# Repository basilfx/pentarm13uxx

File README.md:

pentarm13uxx
============

A small template project (blinking led) for the new lpc1347 (successor of the popular lpc1343).

Including Makefile, linker-script and cmsis and microcontroler header files.

Also includes eagle files for a small breaboardable eval-board.

- - -

####lpc1347 features

* 12k sram (was 8k)
* 64k flash (was 32k)
* 4k EEPROM (new)
* 72Mhz
* USART,I2C,2xSPI
* 12Bit ADC (new)
* USB_MSC, USB_HID, USB_CDC and USB_DFU in rom (new)
* usb-bootloader in rom

- - -

price of the eval board: ~$15

- - -

####BOM:

* C1,C2 : 22pF 0402
* C3,C4 : 100nF 0402
* C6,C8 : 10nF 0402
* C5,C7 : 1µF 0805
* R2,R3,R6,R7 : 150R 0402
* R4,R5 : 33R 0402
* R1,R8,R9 : 15k 0402
* R10 : 1k5 0402
* T1 : Si3102DS SOT23 (or other pfet)
* Q1 : 12Mhz MT (farnell: 1842056)
* IC1 : lpc1347 QFP48 (farnell: 2103477)
* IC2 : LT1763CS8-3.3 SOIC8 (farnell: 1273617)
* X1 : Mini USB Connector SMD (farnell: 1125348)
* X2,X3 : Pin-Header 10 Pin
* X4 : Pin Header 2 Pin
* X5 : Pin Header 4 Pin
* LED1 : RGB LED PLCC4 common annode
* SW1,SW2,RST : MCTAEF-25N (farnell:1605484)

- - -

data sheet  : http://www.nxp.com/documents/data_sheet/LPC1315_16_17_45_46_47.pdf

user manual : http://www.nxp.com/documents/user_manual/UM10524.pdf

toolchain   : https://launchpad.net/gcc-arm-embedded

- - -   

Board top render

 Completed boards, photo by [Dirk Soeteman](http://www.dirksoeteman.nl/)

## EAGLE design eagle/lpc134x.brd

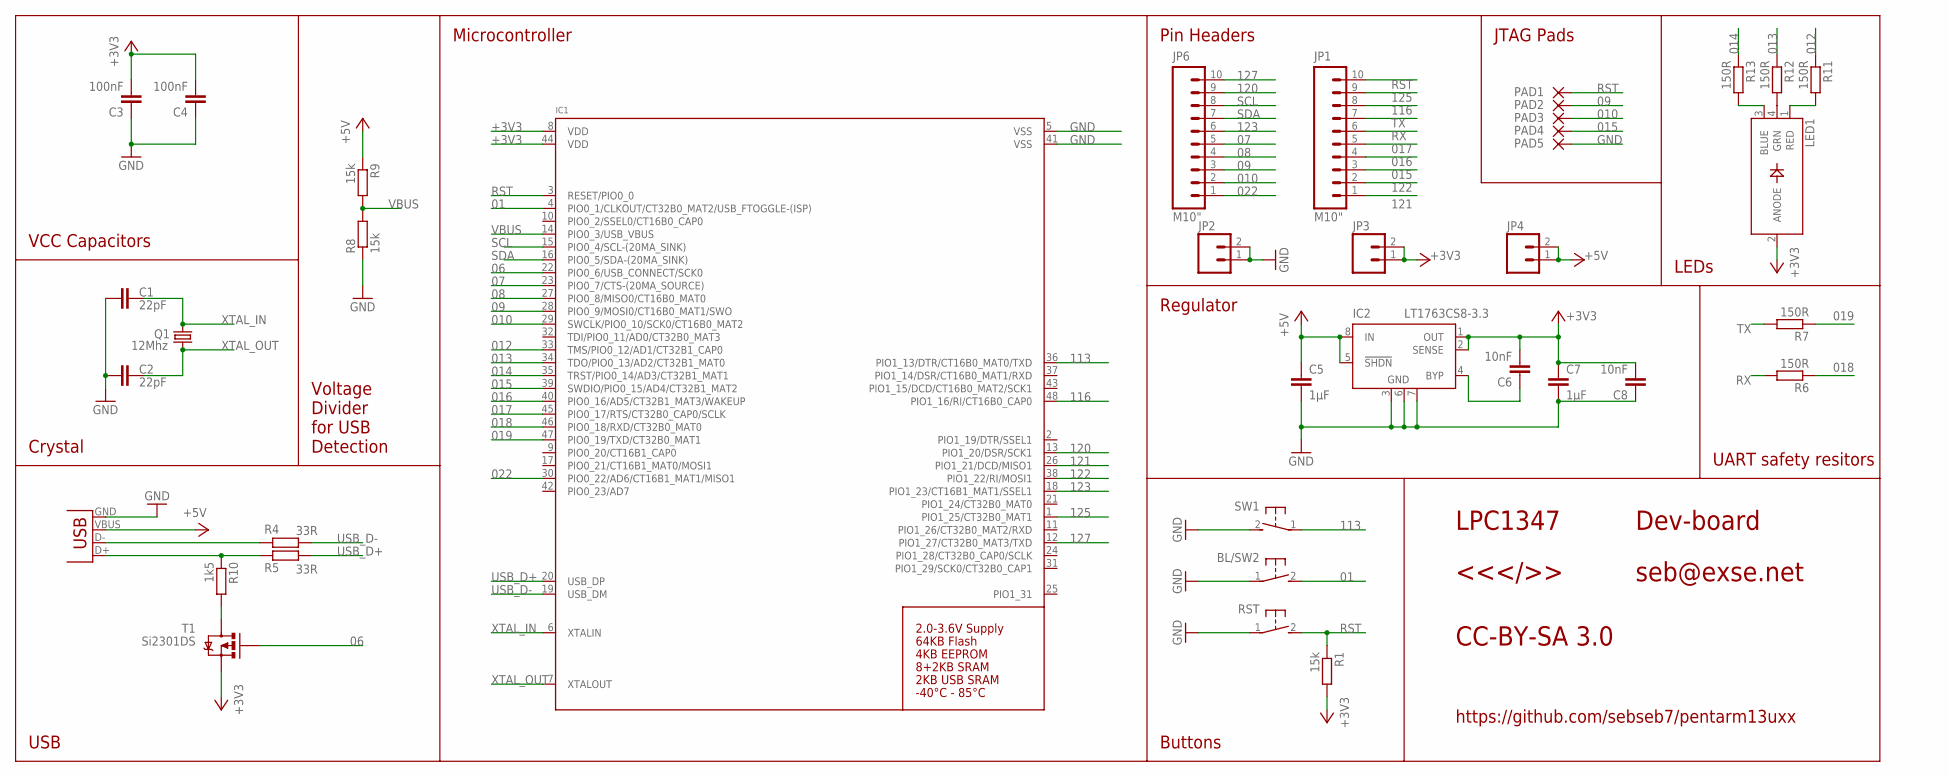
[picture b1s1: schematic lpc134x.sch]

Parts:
BL/SW2: SWITCH_MCTAEF
C1, C2: 22pF; C0402
C3, C4: 100nF; C0402
C5, C7: 1µF; 0805
C6, C8: 10nF; C0402
IC1: LPC1347_QFP48; LQFP48
IC2: LT1763CS8-3.3; SOIC8
JP1, JP6: M10"; 1X10
JP2, JP3, JP4: M02PTH; 1X02
LED1: LED_RGB_PLCC4; RGBLED_PLCC4
PAD1, PAD2, PAD3, PAD4, PAD5: WIREPADSMD1,27-254; SMD1,27-2,54
Q1: 12Mhz; MT
R1, R8, R9: 15k; R0402
R4, R5: 33R; R0402
R6, R7, R11, R12, R13: 150R; R0402
R10: 1k5; R0402
RST: SWITCH_MCTAEF
SW1: SWITCH_MCTAEF
T1: Si2301DS; SOT23
X2: USB-SMD-NS; USB-MINIB-NOSTOP

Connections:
01: BL/SW2.2, IC1.4 (PIO0_1/CLKOUT/CT32B0_MAT2/USB_FTOGGLE-(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)
06: IC1.22 (PIO0_6/USB_CONNECT/SCK0), T1.1 (G)
07: IC1.23 (PIO0_7/CTS-(20MA_SOURCE)), JP6.5
08: IC1.27 (PIO0_8/MISO0/CT16B0_MAT0), JP6.4
09: IC1.28 (PIO0_9/MOSI0/CT16B0_MAT1/SWO), JP6.3, PAD2.1
010: IC1.29 (SWCLK/PIO0_10/SCK0/CT16B0_MAT2), JP6.2, PAD3.1
012: IC1.33 (TMS/PIO0_12/AD1/CT32B1_CAP0), R11.1
013: IC1.34 (TDO/PIO0_13/AD2/CT32B1_MAT0), R12.1
014: IC1.35 (TRST/PIO0_14/AD3/CT32B1_MAT1), R13.1
015: IC1.39 (SWDIO/PIO0_15/AD4/CT32B1_MAT2), JP1.3, PAD4.1
016: IC1.40 (PIO0_16/AD5/CT32B1_MAT3/WAKEUP), JP1.4
017: IC1.45 (PIO0_17/RTS/CT32B0_CAP0/SCLK), JP1.5
018: IC1.46 (PIO0_18/RXD/CT32B0_MAT0), R6.1
019: IC1.47 (PIO0_19/TXD/CT32B0_MAT1), R7.1
022: IC1.30 (PIO0_22/AD6/CT16B1_MAT1/MISO1), JP6.1
113: IC1.36 (PIO1_13/DTR/CT16B0_MAT0/TXD), SW1.1
116: IC1.48 (PIO1_16/RI/CT16B0_CAP0), JP1.8
120: IC1.13 (PIO1_20/DSR/SCK1), JP6.9
121: IC1.26 (PIO1_21/DCD/MISO1), JP1.1
122: IC1.38 (PIO1_22/RI/MOSI1), JP1.2
123: IC1.18 (PIO1_23/CT16B1_MAT1/SSEL1), JP6.6
125: IC1.1 (PIO1_25/CT32B0_MAT1), JP1.9
127: IC1.12 (PIO1_27/CT32B0_MAT3/TXD), JP6.10
+3V3: C3.2, C4.2, C6.2, C7.1, C8.2, IC1.8 (VDD), IC1.44 (VDD), IC2.1 (OUT), IC2.2 (SENSE), JP3.1, JP3.2, LED1.2 (ANODE), R1.2, T1.2 (S)
+5V: C5.1, IC2.5 (!SHDN), IC2.8 (IN), JP4.1, JP4.2, R9.1, X2.VBUS
GND: BL/SW2.1, C1.1, C2.1, C3.1, C4.1, C5.2, C7.2, C8.1, IC1.5 (VSS), IC1.41 (VSS), IC2.3 (GND), IC2.6 (GND), IC2.7 (GND), JP2.1, JP2.2, PAD5.1, R8.1, RST.1, SW1.2, X2.GND
unnamed: LED1.1 (RED), R11.2
unnamed: LED1.4 (GRN), R12.2
unnamed: LED1.3 (BLUE), R13.2
unnamed: R5.2, R10.1, X2.D+
unnamed: R4.2, X2.D-
unnamed: C6.1, IC2.4 (BYP)
unnamed: R10.2, T1.3 (D)
RST: IC1.3 (RESET/PIO0_0), JP1.10, PAD1.1, R1.1, RST.2
RX: JP1.6, R6.2
SCL: IC1.15 (PIO0_4/SCL-(20MA_SINK)), JP6.8
SDA: IC1.16 (PIO0_5/SDA-(20MA_SINK)), JP6.7
TX: JP1.7, R7.2
USB_D+: IC1.20 (USB_DP), R5.1
USB_D-: IC1.19 (USB_DM), R4.1
VBUS: IC1.14 (PIO0_3/USB_VBUS), R8.2, R9.2
XTAL_IN: C1.2, IC1.6 (XTALIN), Q1.3 (2)
XTAL_OUT: C2.2, IC1.7 (XTALOUT), Q1.1

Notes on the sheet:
Pin Headers
Regulator
Buttons
LEDs
UART safety resitors
Microcontroller
Voltage Divider for USB Detection
Crystal
VCC Capacitors
USB
CC-BY-SA 3.0
seb@exse.net
<<</>>
LPC1347
Dev-board
https://github.com/sebseb7/pentarm13uxx
JTAG Pads

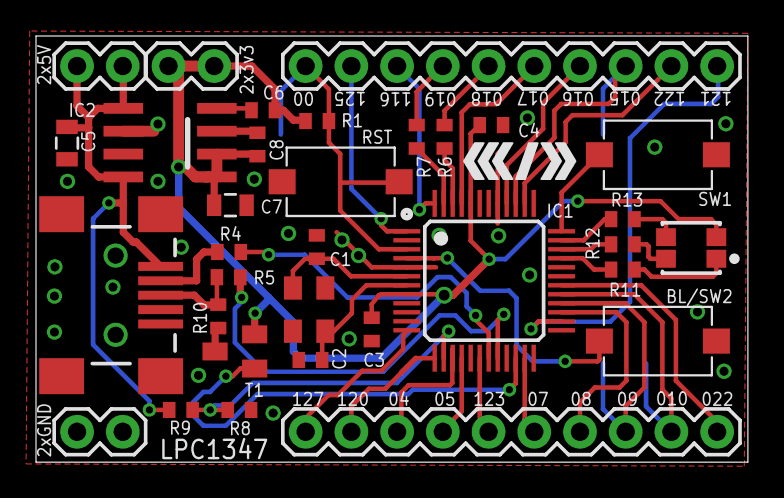
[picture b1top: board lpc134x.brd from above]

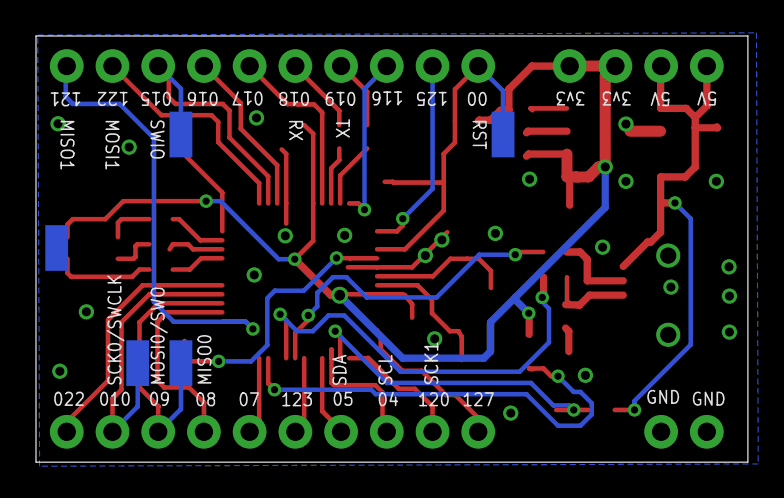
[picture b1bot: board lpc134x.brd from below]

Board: 2 copper layers, 39.5 x 23.7 mm, 39 parts (5 on the bottom side), 43 nets.

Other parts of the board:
U$2: C3D2_LOGO_SMALL

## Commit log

2013-08-14 Improved schematic and board.
    * Replaced 2xLED with RGB LED
    * Replaced third ground pint with 121 (thereby exposing SSP0 and SSP1 completely)
    * Realigned labels on bottom
    * Exposed SWD pads on bottom
2013-08-14 Updated drawings

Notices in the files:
parts and their libraries:
SparkFun-Connectors: Licensing: CC v3.0 Share-Alike You are welcome to use this library for commercial purposes.
